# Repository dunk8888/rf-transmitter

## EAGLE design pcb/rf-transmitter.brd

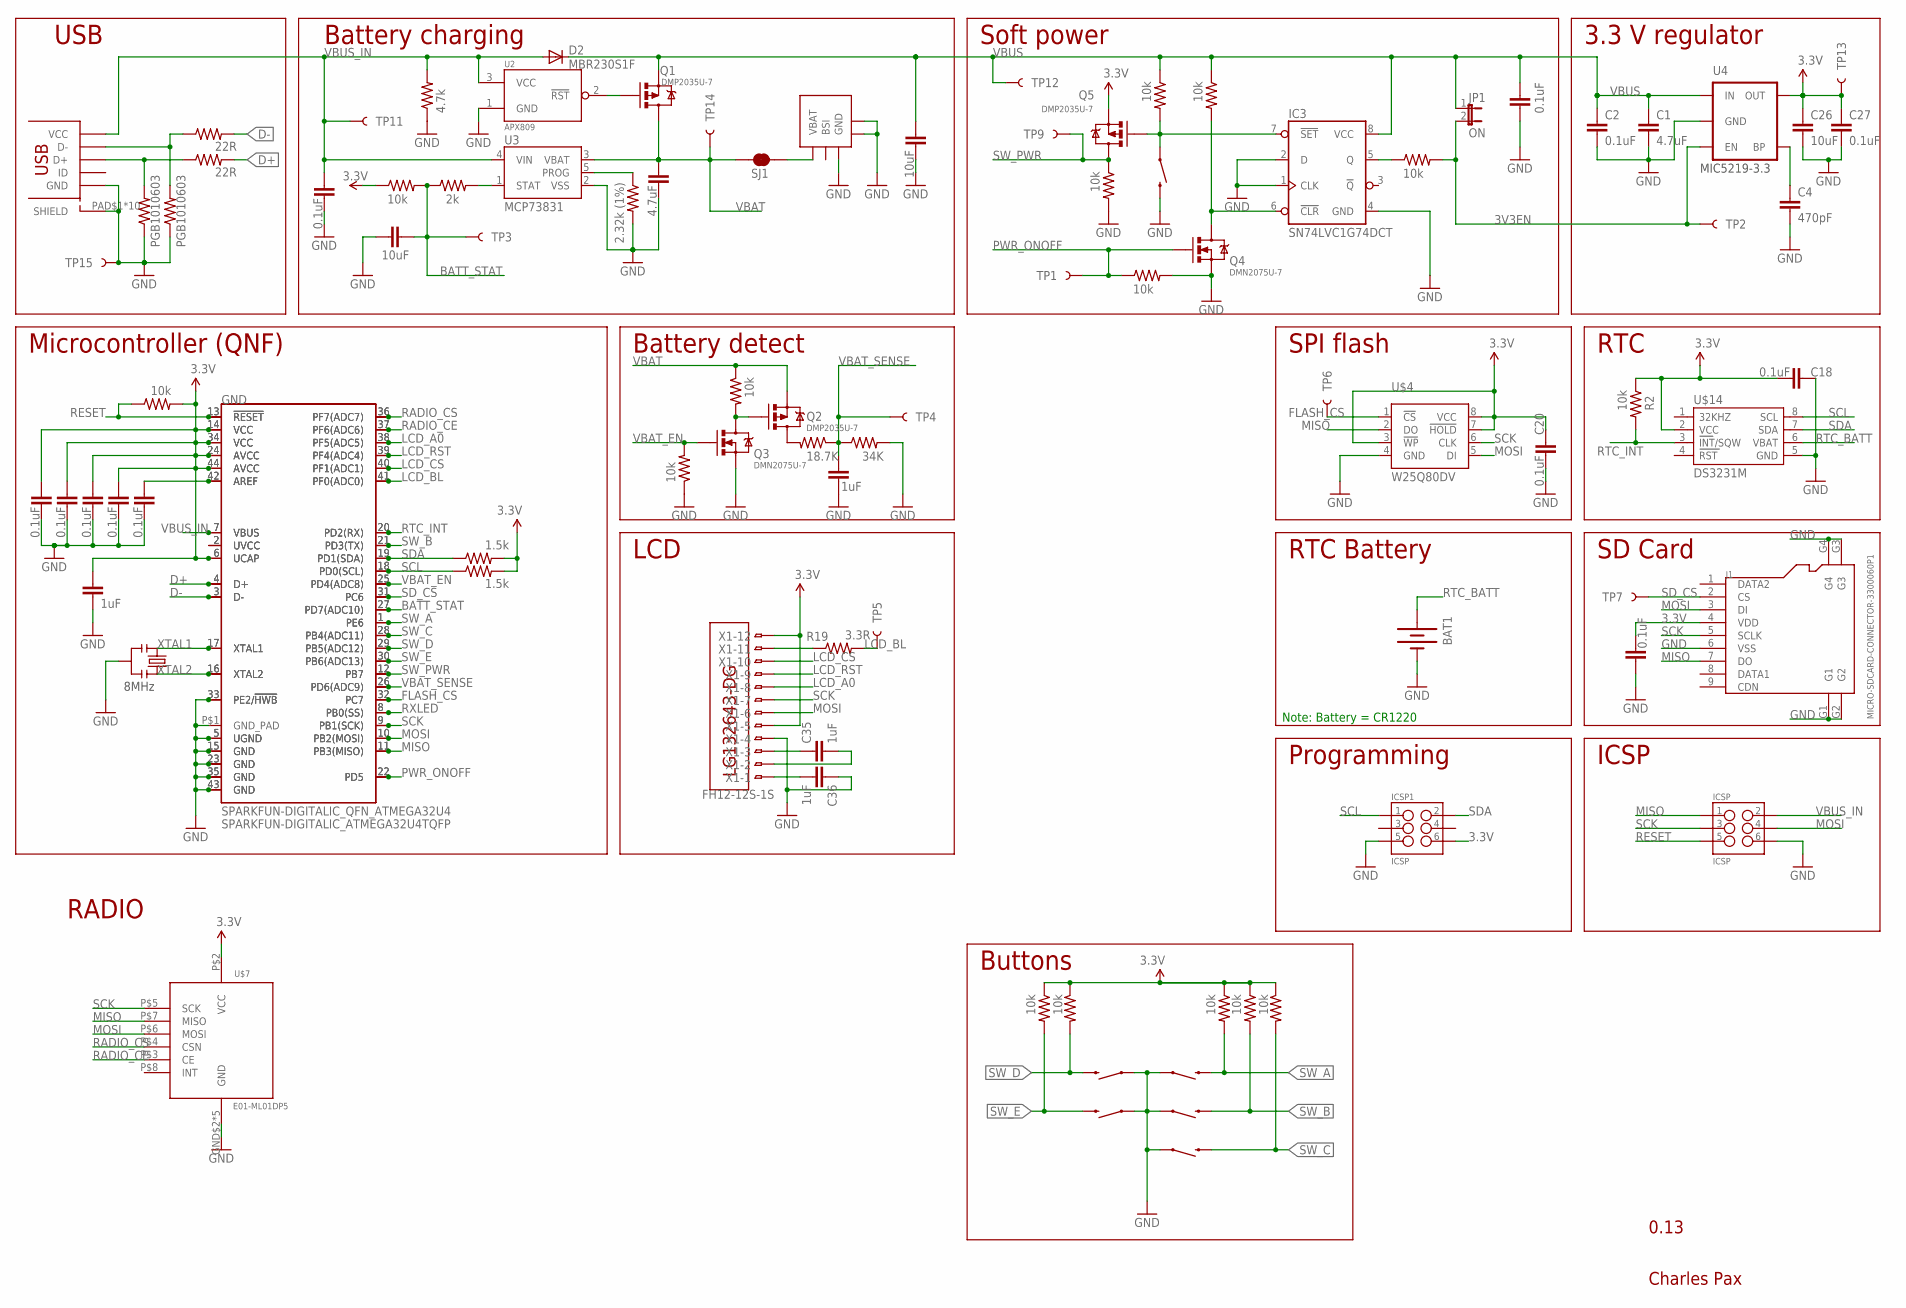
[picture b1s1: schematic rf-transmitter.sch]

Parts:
BAT1: BATTERY12MM; BATTCON_12MM; MPN 3000TR
C1, C9: 4.7uF; SPARKFUN-CAPACITORS_0603-CAP
C2, C3, C5, C6, C18, C20, C21, C27, C28, C32, C33, C34: 0.1uF; SPARKFUN-CAPACITORS_0603-CAP
C4: 470pF; SPARKFUN-CAPACITORS_0603-CAP
C12, C22, C26: 10uF; SPARKFUN-CAPACITORS_0603-CAP
C19, C23, C35, C36: 1uF; SPARKFUN-CAPACITORS_0603-CAP
D2: MBR230S1F; SOD123; MPN MBR230S1F-7
GND: SPARKFUN-DIGITALIC_QFN_ATMEGA32U4; SPARKFUN-DIGITALIC_SPARKFUN-DIGITALIC_QFN-44; MPN ATMEGA32U4-MU
IC3: SN74LVC1G74DCT; SSOP8; MPN SN74LVC1G74DCTR
ICSP, ICSP1: ICSP; SPARKFUN-CONNECTORS_2X3_SMT_POSTS_PAXINSTRUMENT; MPN 95278-101A06LF
J1: MICRO-SDCARD-CONNECTOR-3300060P1; 9P-SMD-W-RING; MPN ST-TF-003A
JP1: ON; SJ_2S-NO; MPN N/A
Q1, Q2, Q5: DMP2035U-7; SOT23; MPN DMP2035U-7
Q3, Q4: DMN2075U-7; SOT23; MPN DMN2075U-7
R1, R2, R4, R5, R6, R7, R8, R11, R12, R15, R16, R18, R21, R22, R23: 10k; SPARKFUN-RESISTORS_0603-RES
R3: 2.32k (1%); SPARKFUN-RESISTORS_0603-RES
R9, R10: 22R; SPARKFUN-RESISTORS_0603-RES
R13, R14: 1.5k; SPARKFUN-RESISTORS_0603-RES
R17: 2k; SPARKFUN-RESISTORS_0603-RES
R19: 3.3R; SPARKFUN-RESISTORS_0603-RES
R20: 18.7K; SPARKFUN-RESISTORS_0603-RES
R24: 34K; SPARKFUN-RESISTORS_0603-RES
R25: 4.7k; SPARKFUN-RESISTORS_0603-RES
S1, S2, S3, S4, S5, S6: SWITCH-MOMENTARY-2SMD; TACTILE_SWITCH_SMD; MPN RS-187R05A2-DS MT RT
SJ1: JUMPER-PAD-2-NC_BY_TRACE; PAD-JUMPER-2-NC_BY_TRACE_YES_SILK; MPN N/A
TP1: PWR_ONOFF; TP_15TH; MPN N/A
TP2: 3V3_EN; TP_15TH; MPN N/A
TP3: BATT_STAT; TP_15TH; MPN N/A
TP4: VBAT_SENSE; TP_15TH; MPN N/A
TP5: LCD_BL; TP_15TH; MPN N/A
TP6: FLASH_CS; TP_15TH; MPN N/A
TP7: SD_CS; TP_15TH; MPN N/A
TP9: SW_PWR; TP_15TH; MPN N/A
TP11: VBUS_IN; TP_15TH; MPN N/A
TP12: VBUS; TP_15TH; MPN N/A
TP13: 3.3V; TP_15TH; MPN N/A
TP14: VBAT; TP_15TH; MPN N/A
TP15: GND; TP_15TH; MPN N/A
U2: APX809; SOT23; MPN APX809-44SAG-7
U3: MCP73831; SOT23-5; MPN MCP73832T-2DCI/OT
U4: MIC5219-3.3V; SOT23-5; MPN MIC5219-3.3YM5 TR
U$1: USB_MICROSMT+THRUHULE; USB_MICRO_THRUHOLE; MPN 10118194-0001LF
U$2: BL-5C-CONNECTOR; MPN BC-4-3P (77H)
U$3: SPARKFUN-DIGITALIC_ATMEGA32U4TQFP; SPARKFUN-DIGITALIC_SPARKFUN-DIGITALIC_TQFP44; MPN ATMEGA32U4-AU
U$4: W25Q80DV; CHARLESPAX_SOIC8M; MPN W25Q80DVSSIG-ND
U$5: LG132643-DG; MPN LG132643-DW
U$7: E01-ML01DP5
U$14: DS3231M; SOIC8; MPN DS3231MZ+
X1: FH12-12S-1S; FH12-12S-1SH; MPN FH12-12S-1SH(55)
Y1: RESONATORSMD; RESONATOR-SMD; MPN CSTCE8M00G52-R0
Z1, Z2: PGB1010603; SPARKFUN-RESISTORS_0603-RES; MPN PGB1010603NRHF

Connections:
3.3V: C5.1, C18.1, C19.1, C20.2, C21.2, C26.1, C27.1, C32.1, C33.1, C34.1, GND.6 (UCAP), GND.14 (VCC), GND.24 (AVCC), GND.34 (VCC), GND.44 (AVCC), ICSP1.6, J1.4 (VDD), Q5.2 (S), R1.1, R2.1, R4.2, R8.1, R11.1, R12.1, R13.2, R14.2, R15.1, R16.1, TP13.P$1, U4.5 (OUT), U$3.6 (UCAP), U$3.14 (VCC), U$3.24 (AVCC), U$3.34 (VCC), U$3.44 (AVCC), U$4.3 (!WP), U$4.7 (!HOLD), U$4.8 (VCC), U$7.P$2 (VCC), U$14.2 (VCC), X1.5, X1.12
3V3EN: JP1.2, R21.2, TP2.P$1, U4.3 (EN)
BATT_STAT: C22.1, GND.27 (PD7(ADC10)), R1.2, R17.1, TP3.P$1, U$3.27 (PD7(ADC10))
D+: GND.4 (D+), R9.2, U$3.4 (D+)
D-: GND.3 (D-), R10.2, U$3.3 (D-)
FLASH_CS: GND.32 (PC7), TP6.P$1, U$3.32 (PC7), U$4.1 (!CS)
GND: BAT1.GND (-), C1.2, C2.2, C3.2, C4.2, C5.2, C6.2, C9.2, C12.2, C18.2, C19.2, C20.1, C21.1, C22.2, C23.2, C26.2, C27.2, C28.2, C32.2, C33.2, C34.2, C36.1, GND.5 (UGND), GND.15 (GND), GND.23 (GND), GND.33 (PE2/!HWB), GND.35 (GND), GND.43 (GND), GND.P$1 (GND_PAD), IC3.1 (CLK), IC3.2 (D), IC3.4 (GND), ICSP.6, ICSP1.5, J1.6 (VSS), J1.G1, J1.G2, J1.G3, J1.G4, Q3.2 (S), Q4.2 (S), R3.2, R18.2, R22.2, R23.1, R24.2, R25.1, S1.1, S2.1, S3.1, S4.1, S5.1, S6.3 (2), TP15.P$1, U2.1 (GND), U3.2 (VSS), U4.2 (GND), U$1.PAD$1 (SHIELD), U$1.PAD$2 (SHIELD), U$1.PAD$3 (SHIELD), U$1.PAD$4 (SHIELD), U$1.PAD$5 (SHIELD), U$1.PAD$6 (SHIELD), U$1.PAD$7 (SHIELD), U$1.PAD$8 (SHIELD), U$1.PAD$9 (SHIELD), U$1.PAD$10 (SHIELD), U$1.PIN$5 (GND), U$2.P$3 (GND), U$2.P$4, U$2.P$5, U$3.5 (UGND), U$3.15 (GND), U$3.23 (GND), U$3.33 (PE2/!HWB), U$3.35 (GND), U$3.43 (GND), U$4.4 (GND), U$7.GND$2 (GND), U$7.GND$3 (GND), U$7.GND$4 (GND), U$7.GND$5 (GND), U$7.P$1 (GND), U$14.5 (GND), X1.4, Y1.2, Z1.1, Z2.1
LCD_A0: GND.38 (PF5(ADC5)), U$3.38 (PF5(ADC5)), X1.8
LCD_BL: GND.41 (PF0(ADC0)), R19.2, TP5.P$1, U$3.41 (PF0(ADC0))
LCD_CS: GND.40 (PF1(ADC1)), U$3.40 (PF1(ADC1)), X1.10
LCD_RST: GND.39 (PF4(ADC4)), U$3.39 (PF4(ADC4)), X1.9
MISO: GND.11 (PB3(MISO)), ICSP.1, J1.7 (DO), U$3.11 (PB3(MISO)), U$4.2 (DO), U$7.P$7 (MISO)
MOSI: GND.10 (PB2(MOSI)), ICSP.4, J1.3 (DI), U$3.10 (PB2(MOSI)), U$4.5 (DI), U$7.P$6 (MOSI), X1.6
unnamed: C4.1, U4.4 (BP)
unnamed: R17.2, U3.1 (STAT)
unnamed: R19.1, X1.11
unnamed: R3.1, U3.5 (PROG)
unnamed: SJ1.2, U$2.P$1 (VBAT)
unnamed: Q1.1 (G), U2.2 (!RST)
unnamed: C3.1, GND.42 (AREF), U$3.42 (AREF)
unnamed: GND.2 (UVCC), U$3.2 (UVCC)
unnamed: Q2.3 (D), R20.2
unnamed: IC3.7 (!SET), Q5.1 (G), R6.2, S6.1
unnamed: Q2.1 (G), Q3.3 (D), R5.2
unnamed: IC3.6 (!CLR), Q4.3 (D), R7.2
unnamed: IC3.5 (Q), R21.1
unnamed: R10.1, U$1.PIN$2 (D-), Z2.2
unnamed: R9.1, U$1.PIN$3 (D+), Z1.2
unnamed: C35.1, X1.3
unnamed: C35.2, X1.2
unnamed: C36.2, X1.1
PWR_ONOFF: GND.22 (PD5), Q4.1 (G), R22.1, TP1.P$1, U$3.22 (PD5)
RADIO_CE: GND.37 (PF6(ADC6)), U$3.37 (PF6(ADC6)), U$7.P$3 (CE)
RADIO_CS: GND.36 (PF7(ADC7)), U$3.36 (PF7(ADC7)), U$7.P$4 (CSN)
RESET: GND.13 (!RESET), ICSP.5, R4.1, U$3.13 (!RESET)
RTC_BATT: BAT1.PWR@1 (+), U$14.6 (VBAT)
RTC_INT: GND.20 (PD2(RX)), R2.2, U$3.20 (PD2(RX)), U$14.3 (INT/SQW)
RXLED: GND.8 (PB0(SS)), U$3.8 (PB0(SS))
SCK: GND.9 (PB1(SCK)), ICSP.3, J1.5 (SCLK), U$3.9 (PB1(SCK)), U$4.6 (CLK), U$7.P$5 (SCK), X1.7
SCL: GND.18 (PD0(SCL)), ICSP1.1, R14.1, U$3.18 (PD0(SCL)), U$14.8 (SCL)
SDA: GND.19 (PD1(SDA)), ICSP1.2, R13.1, U$3.19 (PD1(SDA)), U$14.7 (SDA)
SD_CS: GND.31 (PC6), J1.2 (CS), TP7.P$1, U$3.31 (PC6)
SW_A: GND.1 (PE6), R8.2, S3.3 (2), U$3.1 (PE6)
SW_B: GND.21 (PD3(TX)), R11.2, S2.3 (2), U$3.21 (PD3(TX))
SW_C: GND.28 (PB4(ADC11)), R12.2, S1.3 (2), U$3.28 (PB4(ADC11))
SW_D: GND.29 (PB5(ADC12)), R15.2, S4.3 (2), U$3.29 (PB5(ADC12))
SW_E: GND.30 (PB6(ADC13)), R16.2, S5.3 (2), U$3.30 (PB6(ADC13))
SW_PWR: GND.12 (PB7), Q5.3 (D), R18.1, TP9.P$1, U$3.12 (PB7)
VBAT: C9.1, Q1.3 (D), Q2.2 (S), R5.1, SJ1.1, TP14.P$1, U3.3 (VBAT)
VBAT_EN: GND.25 (PD4(ADC8)), Q3.1 (G), R23.2, U$3.25 (PD4(ADC8))
VBAT_SENSE: C23.1, GND.26 (PD6(ADC9)), R20.1, R24.1, TP4.P$1, U$3.26 (PD6(ADC9))
VBUS: C1.1, C2.1, C12.1, C28.1, D2.C, IC3.8 (VCC), JP1.1, Q1.2 (S), R6.1, R7.1, TP12.P$1, U4.1 (IN)
VBUS_IN: C6.1, D2.A, GND.7 (VBUS), ICSP.2, R25.2, TP11.P$1, U2.3 (VCC), U3.4 (VIN), U$1.PIN$1 (VCC), U$3.7 (VBUS)
XTAL1: GND.17 (XTAL1), U$3.17 (XTAL1), Y1.1
XTAL2: GND.16 (XTAL2), U$3.16 (XTAL2), Y1.3

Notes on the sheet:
MIC5219-3.3
8MHz
USB
Battery charging
Soft power
3.3 V regulator
RTC
LCD
Buttons
Microcontroller (QNF)
ICSP
0.13
Programming
RTC Battery
Charles Pax
SPI flash
SD Card
Battery detect
Note: Battery = CR1220
RADIO

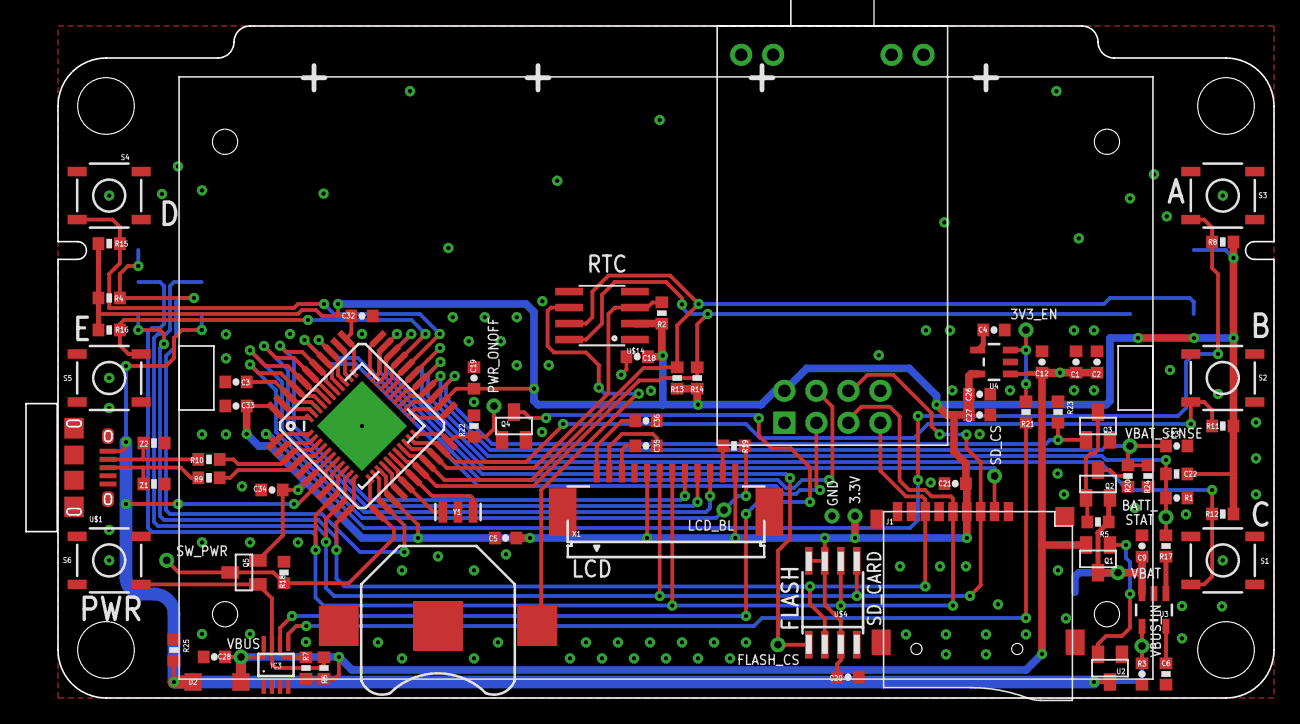
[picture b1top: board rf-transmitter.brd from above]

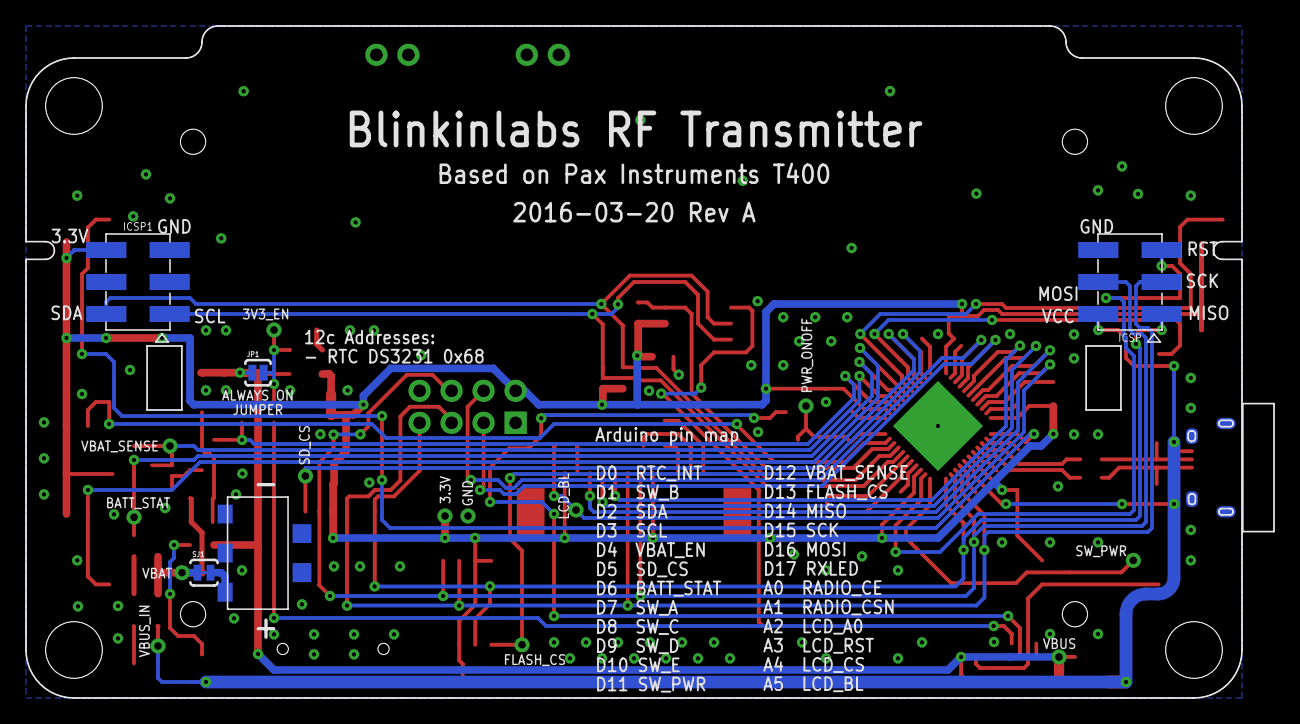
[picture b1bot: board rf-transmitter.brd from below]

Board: 2 copper layers, 99.1 x 53.3 mm, 94 parts (9 on the bottom side), 55 nets.

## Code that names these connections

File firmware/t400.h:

// Hardware definitions


#define DISPLAY_HEIGHT  64    // Height of the display
#define CHARACTER_SPACING 5   // Width of a character+space to next character


// Pin definitions
#define BUTTON_B_PIN         7
#define BUTTON_A_PIN         1
// SDA                       2
// SCL                       3
#define VBAT_EN              4  // Enable VBAT_SENSE
#define SD_CS                5
#define BATT_STAT            A7    // Battery status pin
#define RTC_INT              0
#define BUTTON_C_PIN         8
#define BUTTON_D_PIN         9
#define BUTTON_E_PIN        10
#define PWR_ONOFF_PIN       30   // Power on/off pin turns board power off (active high)
#define VBAT_SENSE          A11  // Battery voltage /2 (D12)
// #define FLASH_CS            13
// MISO                     14
// SCK                      15
// MOSI                     16
#define BUTTON_POWER_PIN    11


#define RADIO_CE            A0       // D12
#define RADIO_CSN           A1       // D11

#define LCD_A0              A2
#define LCD_RST             A3
#define LCD_CS              A4
#define LCD_BACKLIGHT_PIN   A5   // LCD backlight on pin


#define LCD_CONTRAST     0x018*7  // Sets the LCD contrast


// Data packet format:
// 0: Command (0: hello, 1: start LED timer)
// 1: On time, in minutes (1-60)
// 2: Sleep time, in seconds (1-10)
// 3: Brightness (0-255)
// 4,5: Reserved
// 6: CRC

#define COMMAND_LENGTH 7

#define COMMAND_HELLO   0
#define COMMAND_SQUACK  1

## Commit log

2016-03-20 Add RevA board
2016-03-20 Test firmware, has standby and tx modes

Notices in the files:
parts and their libraries:
SparkFun-PowerIC: Licensing: CC v3.0 Share-Alike You are welcome to use this library for commercial purposes.
